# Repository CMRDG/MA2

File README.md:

View this project on [CADLAB.io](https://cadlab.io/project/2232). 

# MA2

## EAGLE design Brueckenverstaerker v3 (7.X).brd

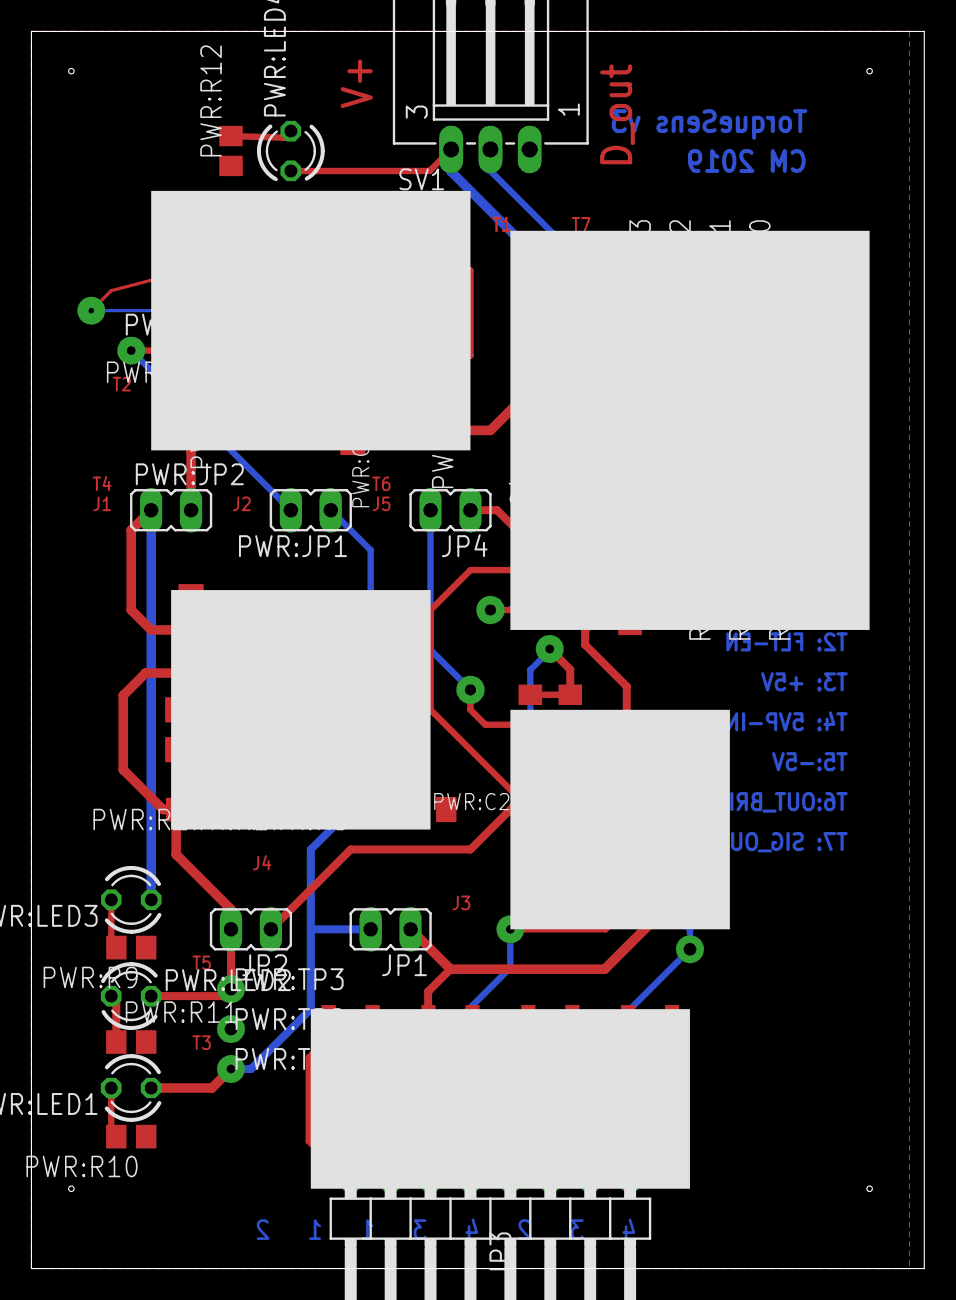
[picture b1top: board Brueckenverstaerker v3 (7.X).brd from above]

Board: 2 copper layers, 56.8 x 78.7 mm, 63 parts (0 on the bottom side), 42 nets.

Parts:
C1, C2, C3: 0.1uF; C0805
C4, C5: C0805
JP1, JP2, JP4: JP1
JP3: 1X08/90
PWR:C1: 1uF; C0805K
PWR:C2, PWR:C3: 4.7uF; C0805K
PWR:C4: 1000nF; C0805K
PWR:C5, PWR:C7: 10uF; C0805K
PWR:C6: 0.1uF; C0805K
PWR:JP1, PWR:JP2: JP1
PWR:L1: 2.2uH; L2825P
PWR:LED1, PWR:LED2, PWR:LED3, PWR:LED4: LED3MM
PWR:PROTECT-IC: SON50P300X300X100-11N
PWR:R1: 120k; R0805
PWR:R2: 487k; R0805
PWR:R3: 365k; R0805
PWR:R4: 10k; R0805
PWR:R5: 119.52k; R0805
PWR:R6: 5.11k; R0805
PWR:R7: 34.72k; R0805
PWR:R8: 22k; R0805
PWR:R9, PWR:R10, PWR:R11, PWR:R12: 200; R0805
PWR:SPLIT: TPS65135TPS65135; QFN50P300X300X80-17N
PWR:TP1, PWR:TP2, PWR:TP3, PWR:TP4, PWR:TP5: PTR1B1,27; B1,27
R1: 350; R0805
R2, R3: 18.2k; R0805
R4, R5, R6, R7: 3223J
R8, R9, R10, R11, R12, R13, R14, R15, R16: 18.2k; R0603
S1: SS-10-15SPE; SW_SS-10-15SPE
SV1: L03P
TP1: PTR1B1,27; B1,27
U1: LINEAR_TECHNOLOGY_LTC2050IS5LINEAR_TECHNOLOGY_LTC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; LINEAR_TECHNOLOGY_LTC2050IS5_0
U2: TI_NATIONAL_SEMICONDUCTOR_LMP7707MF-NOPBTI_NATION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; TI_NATIONAL_SEMICONDUCTOR_LMP7707MF-NOPB_1

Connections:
GND: C1.2, C2.2, C4.2, C5.2, JP3.4, PWR:C1.2, PWR:C2.2, PWR:C3.1, PWR:C4.1, PWR:C5.1, PWR:C6.1, PWR:C7.1, PWR:PROTECT-IC.6, PWR:R9.1, PWR:R10.1, PWR:R11.2, PWR:R12.1, PWR:SPLIT.5, PWR:SPLIT.11, PWR:SPLIT.12, PWR:TP2.TP, R1.1, R2.2, R6.3, R8.2, SV1.1
M+: C1.1, JP3.2, R2.1, R7.3, U1.3
M-: C3.1, JP3.8, R3.1, R4.3, U1.4
unnamed: JP3.7, R4.2
unnamed: R9.1, S1.9
unnamed: R8.1, R9.2, R10.2, R11.2, R12.2, R13.2, R14.2, R15.2, R16.2, S1.1, U2.4
unnamed: JP3.5, R5.2
unnamed: R10.1, S1.8
unnamed: JP3.3, R6.2
unnamed: R11.1, S1.7
unnamed: JP3.1, R7.2
unnamed: JP4.1, U2.3
unnamed: R12.1, S1.6
unnamed: R13.1, S1.5
unnamed: R14.1, S1.4
unnamed: R15.1, S1.3
unnamed: R16.1, S1.2
OUT-BRIDGE: C3.2, JP4.2, R3.2, U1.1
OUTAMP: S1.C, SV1.2, TP1.TP, U2.1
PWR:FLT: PWR:JP1.2, PWR:PROTECT-IC.9, PWR:R4.1, PWR:TP5.TP
PWR:N$1: PWR:PROTECT-IC.2, PWR:R5.1, PWR:R6.1
PWR:N$2: PWR:L1.1, PWR:SPLIT.15, PWR:SPLIT.16
PWR:N$3: PWR:L1.2, PWR:SPLIT.13, PWR:SPLIT.14
PWR:N$4: PWR:C6.2, PWR:PROTECT-IC.8
PWR:N$5: PWR:R1.1, PWR:R3.2, PWR:SPLIT.7
PWR:N$6: PWR:R1.2, PWR:R2.1, PWR:SPLIT.6
PWR:N$7: PWR:PROTECT-IC.5, PWR:R7.2, PWR:R8.1
PWR:N$8: PWR:C4.2, PWR:SPLIT.4
PWR:N$9: PWR:PROTECT-IC.7, PWR:R8.2
PWR:N$10: PWR:LED3.K, PWR:R9.2
PWR:N$11: PWR:LED1.K, PWR:R10.2
PWR:N$13: PWR:LED2.A, PWR:R11.1
PWR:N$15: PWR:JP1.1, PWR:SPLIT.8
PWR:N$16: PWR:C7.2, PWR:JP2.2, PWR:PROTECT-IC.10, PWR:R4.2
PWR:N$17: PWR:LED4.K, PWR:R12.2
PWR:OVP: PWR:PROTECT-IC.3, PWR:R6.2, PWR:R7.1
PWR:VOUT-VIN: PWR:C5.2, PWR:JP2.1, PWR:LED3.A, PWR:SPLIT.1
V+IN: PWR:C1.1, PWR:LED4.A, PWR:PROTECT-IC.1, PWR:R5.2, PWR:TP4.TP, SV1.3
V+OUT: C2.1, C5.1, JP1.1, JP3.6, R5.3, U1.5, U2.5
V+OUT_SPLIT: JP1.2, PWR:C2.1, PWR:LED1.A, PWR:R3.1, PWR:SPLIT.9, PWR:SPLIT.10, PWR:TP1.TP
V-OUT: C4.1, JP2.1, R1.2, U1.2, U2.2
V-OUT_SPLIT: JP2.2, PWR:C3.2, PWR:LED2.K, PWR:R2.2, PWR:SPLIT.2, PWR:SPLIT.3, PWR:TP3.TP

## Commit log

2019-10-23 Backlink to CADLAB.io has been added.
2019-10-23 change1
    change1
